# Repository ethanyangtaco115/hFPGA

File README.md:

# hFPGA (WIP)

A modified PicoEVB FPGA board made for rapid prototyping, DIY projects, and making FPGAs more accessible to hobbyists
Sub-System of our Flash LiDAR Project

## Acknowledgements

 - [Major Credit to PicoEVB creators, who made the base schematic for our design.](https://github.com/RHSResearchLLC/PicoEVB/tree/master)

## Features

- 78 Total I/O Pins
- SPI Flash Boot capability
- Integrated USB-JTAG support
- 4 ADC Pins
- 4 Clock Output Pins
- 4 3.3v PWR Pins
- 6 True Single-Ended GPIO Pins
- 15 Differential Lines, with Pseudo-Single Ended capability
- 24 GND Pins

# Authors

Created by [Ethan Yang](https://github.com/ethanyangtaco115) & [Stanley Wang](https://github.com/GhostWinterOwl)

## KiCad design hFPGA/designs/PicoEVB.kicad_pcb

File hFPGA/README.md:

# hFPGA (WIP)

A modified PicoEVB FPGA board made for rapid prototyping, DIY projects, and making FPGAs more accessible to hobbyists

## Acknowledgements

 - [Major Credit to PicoEVB creators, who made the base schematic for our design.](https://github.com/RHSResearchLLC/PicoEVB/tree/master)

## Features

- 78 Total I/O Pins
- SPI Flash Boot capability
- Integrated USB-JTAG support
- 4 ADC Pins
- 4 Clock Output Pins
- 4 3.3v PWR Pins
- 6 True Single-Ended GPIO Pins
- 15 Differential Lines, with Pseudo-Single Ended capability
- 24 GND Pins

# Authors

Created by [Ethan Yang](https://github.com/ethanyangtaco115) & [Stanley Wang](https://github.com/GhostWinterOwl)

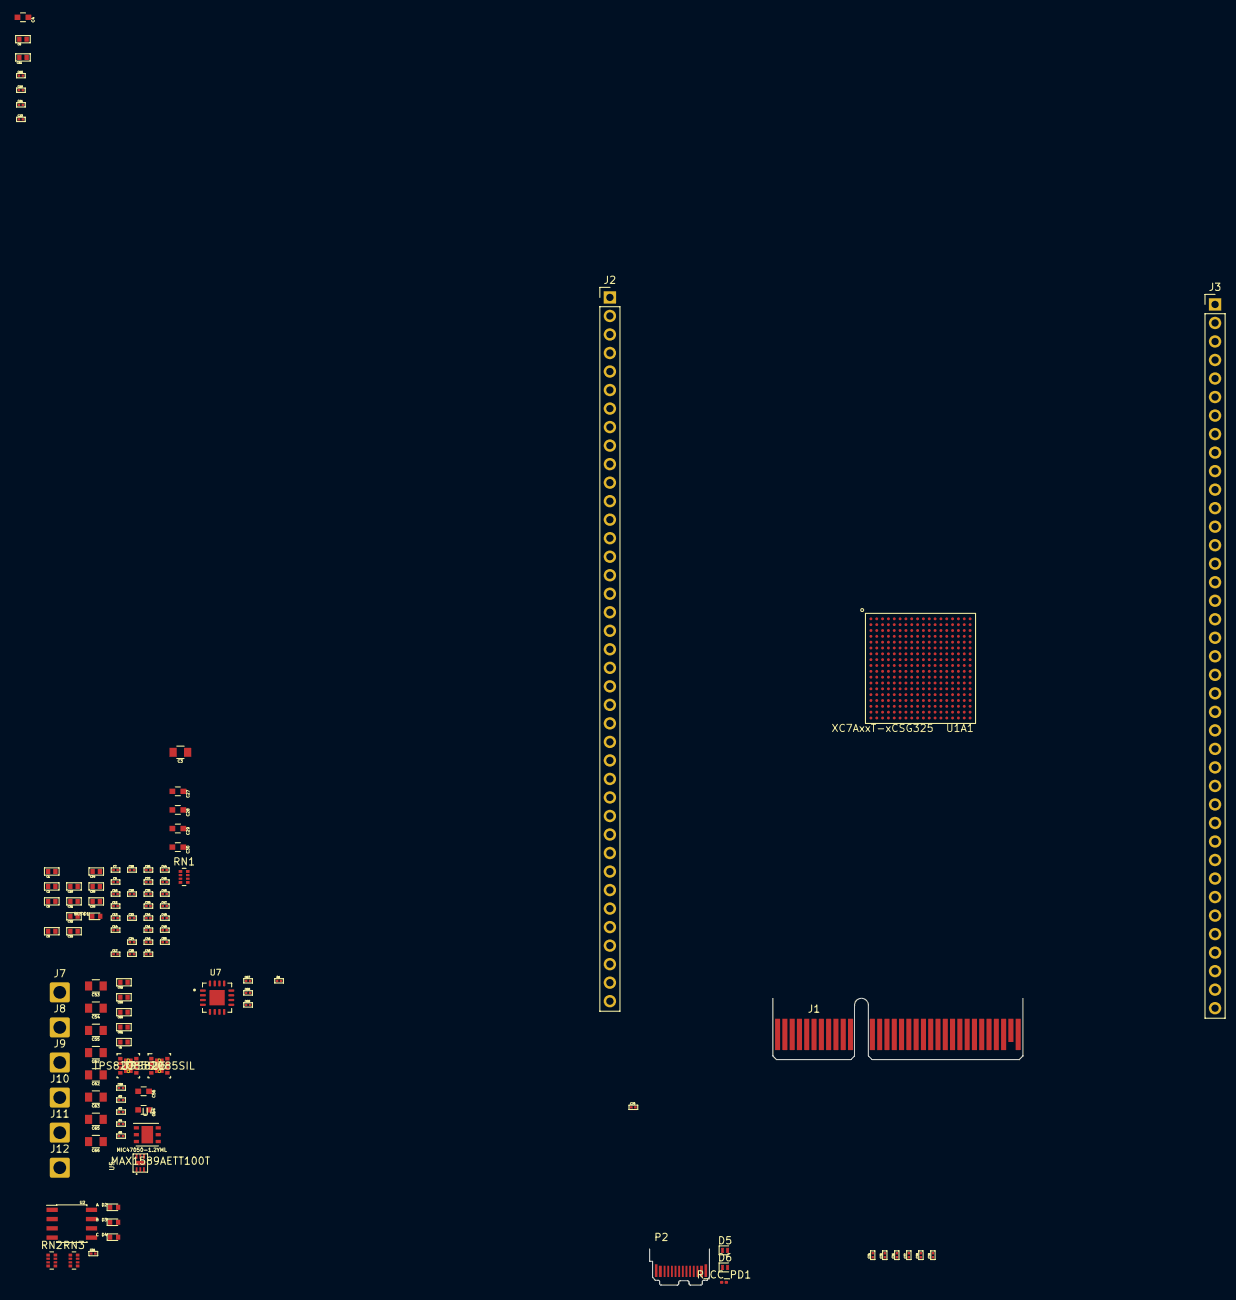
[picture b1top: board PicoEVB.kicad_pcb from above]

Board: 4 copper layers, 109 parts (0 on the bottom side), 35 nets, no tracks yet.

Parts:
C1, C2, C5, C6, C8, C11, C15, C31, C32, C33, C34, C35, C36: 4.7uf; c_0402
C3, C53, C54, C55, C57, C62, C63, C65, C66: 100uf; C_0805
C4, C27, C28, C29, C30: 47uf; C_0603
C7, C12, C16, C17, C18, C19, C20, C21, C22, C23, C24, C25, C26, C37, C38, C39, C40, C41, C42, C43, C44, C45, C46, C47, C48, C49, C50, C70: 0.47uf; c_0201_least
C9, C10, C13, C14, C51, C59, C67, C68, C69, C74, C75, C76, C77, C78, C79: 0.1uf; c_0201_least
C52, C58, C60, C61: 10uf; c_0402
C56, C64: 22uf; C_0603
D1: BUSY; LED_0402
D2: A; LED_0402
D3: B; LED_0402
D4: C; LED_0402
D5, D6: PESD5V0S1UL; D_SOD-882
J1: Bus_PCI_Express_x4; BUS_PCIexpress_x4
J2, J3: 2.54mm Through-Hole Socket; PinHeader_1x39_P2.54mm_Vertical
J7: 3P3; SolderWire-1sqmm_1x01_D1.4mm_OD2.7mm
J8: 1P8; SolderWire-1sqmm_1x01_D1.4mm_OD2.7mm
J9, J11: 1P0; SolderWire-1sqmm_1x01_D1.4mm_OD2.7mm
J10: 1P2; SolderWire-1sqmm_1x01_D1.4mm_OD2.7mm
J12: GND; SolderWire-1sqmm_1x01_D1.4mm_OD2.7mm
L1: 330; r_0402
P2: USB_C_Plug_USB2.0; USB_C_Plug_JAE_DX07P024AJ1
R1: 100; r_0201_least
R2: 124k; r_0201_least
R3, R5: 100k; r_0201_least
R4: 24.9k; r_0201_least
RN1, RN3: 4.7K; R_Array_Convex_4x0402
RN2: 681; R_Array_Convex_4x0402
R_CC_PD1: 5.1k; R_0201_0603Metric
U1A1: XC7AxxT-xCSG325; CSG-324
U2: S25Q; SOIC-8_3.9x4.9mm_Pitch1.27mm
U3, U6: TPS82085SIL; TPS82084SILR
U4: MAX1589AETT100T
U5: MIC47050-1.2YML; MIC47050-DFN-6-2MM
U7: FT230XQ; QFN65P400X400X80-17N

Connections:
BUSY_LED_PU: D1.2 (A), RN2.5 (R4.2)
FPGA_CCLK_0_B: U1A1.E8 (CCLK_0), U2.6 (SCK)
GND: C1.2, C2.2, C3.2, C4.2, C5.2, C6.2, C7.2, C8.2, C9.2, C10.2, C11.2, C12.2, C13.2, C14.2, C15.2, C16.2, C17.2, C18.2, C19.2, C20.2, C21.2, C22.2, C23.2, C24.2, C25.2, C26.2, C27.2, C28.2, C29.2, C30.2, C31.2, C32.2, C33.2, C34.2, C35.2, C36.2, C37.2, C38.2, C39.2, C40.2, C41.2, C42.2, C43.2, C44.2, C45.2, C46.2, C47.2, C48.2, C49.2, C50.2, C51.2, C52.2, C53.2, C54.2, C55.2, C56.2, C57.2, C58.2, C59.2, C60.2, C61.2, C62.2, C63.2, C64.2, C65.2, C66.2, C67.2, C68.2, C69.2, C70.1, J1.A4 (GND), J1.A12 (GND), J1.A15 (GND), J1.A18 (GND), J1.A20 (GND), J1.A23 (GND), J1.A24 (GND), J1.A27 (GND), J1.A28 (GND), J1.A31 (GND), J1.B4 (GND), J1.B7 (GND), J1.B13 (GND), J1.B16 (GND), J1.B18 (GND), J1.B21 (GND), J1.B22 (GND), J1.B25 (GND), J1.B26 (GND), J1.B29 (GND), J1.B32 (GND), J2.2, J2.5, J2.8, J2.11, J2.14, J2.17, J2.20, J2.23, J2.26, J2.29, J2.32, J2.35, J2.38, J3.8, J3.11, J3.14, J3.17, J3.20, J3.23, J3.26, J3.29, J3.32, J3.35, J3.38, J12.1, P2.A1 (GND), P2.A12 (GND), P2.B1 (GND), P2.B12 (GND), P2.S1 (SHIELD), R3.2, R5.2, R_CC_PD1.2, U1A1.E11 (VCCBATT_0), U1A1.F13 (M2_0), U1A1.J9 (GNDADC_0), U1A1.K9 (VREFN_0), U1A1.K10 (VP_0), U1A1.L9 (VN_0), U1A1.L10 (VREFP_0), U1A1.M9 (DXN_0), U1A1.M10 (DXP_0), U1A1.R11 (M1_0), U2.4 (GND), U3.5 (GND), U3.6 (GND), U3.9 (PAD), U4.4 (GND), U4.7 (GND), U5.2 (GND), U5.7 (GND), U6.5 (GND), U6.6 (GND), U6.9 (PAD), U7.3 (GND), U7.13 (GND), U7.17 (GND)
JTAG_TCK_B: U1A1.F8 (TCK_0), U7.15 (TXD)
JTAG_TDI_B: U1A1.T9 (TDI_0), U7.2 (RXD)
JTAG_TDO_B: U1A1.T8 (TDO_0), U7.16 (~RTS)
JTAG_TMS_B: U1A1.R8 (TMS_0), U7.4 (~CTS)
unnamed: D1.1 (K), RN1.8 (R1.2), U1A1.F12 (DONE_0)
unnamed: D2.2 (A), RN2.6 (R3.2)
unnamed: D3.2 (A), RN2.8 (R1.2)
unnamed: D4.2 (A), RN2.7 (R2.2)
unnamed: D5.1 (K), P2.A7 (D-)
unnamed: D6.1 (K), P2.A6 (D+)
unnamed: C77.2, J1.B15 (PETn0)
unnamed: C79.2, J1.B20 (PETn1)
unnamed: C76.2, J1.B14 (PETp0)
unnamed: C78.2, J1.B19 (PETp1)
unnamed: C74.1, J1.A13 (REFCLK+)
unnamed: C75.1, J1.A14 (REFCLK-)
unnamed: P2.A5 (CC), R_CC_PD1.1
unnamed: RN1.7 (R2.2), U1A1.T10 (INIT_B_0)
unnamed: RN1.6 (R3.2), U1A1.P10 (PROGRAM_B_0)
unnamed: RN3.7 (R2.2), U2.7 (DQ3)
unnamed: RN3.6 (R3.2), U2.3 (DQ2)
unnamed: RN3.5 (R4.2), U2.1 (~CS)
unnamed: R2.2, R3.1, U3.7 (FB)
unnamed: C56.1, C57.1, L1.2, R2.1, U3.8 (VOUT), U4.5 (SHDN#), U4.6 (IN), U5.3 (IN)
unnamed: R4.2, R5.1, U6.7 (FB)
P1V0_MGTAVCC_B: C1.1, C9.1, C13.1, C60.1, C62.1, J9.1, U4.1 (OUT)
P1V0_VCC_FPGA_B: C3.1, C5.1, C7.1, C8.1, C12.1, C15.1, C17.1, C18.1, C20.1, C22.1, C24.1, C25.1, C26.1, C64.1, C65.1, C66.1, J11.1, R4.1, U6.8 (VOUT)
P1V2_MGTAVTT_B: C2.1, C10.1, C14.1, C61.1, C63.1, J10.1, R1.2, U5.4 (OUT)
P1V8_FPGA_VCCAUX_B: C4.1, C6.1, C11.1, C16.1, C19.1, C21.1, C23.1, J8.1, L1.1, U1A1.J10 (VCCADC_0)
USB_2+: D6.2 (A), U7.6 (USBDP)
USB_2-: D5.2 (A), U7.7 (USBDM)
VCC_BANK14_B: C27.1, C28.1, C29.1, C30.1, C31.1, C32.1, C33.1, C34.1, C35.1, C36.1, C37.1, C38.1, C39.1, C40.1, C41.1, C42.1, C43.1, C44.1, C45.1, C46.1, C47.1, C48.1, C49.1, C50.1, C51.1, C52.1, C53.1, C54.1, C55.1, C58.1, C59.1, C67.1, C68.1, C69.1, C70.2, J1.A9 (+3.3V), J1.A10 (+3.3V), J1.B8 (+3.3V), J2.1, J2.39, J3.1, J3.39, J7.1, RN1.1 (R1.1), RN1.2 (R2.1), RN1.3 (R3.1), RN1.4 (R4.1), RN2.1 (R1.1), RN2.2 (R2.1), RN2.3 (R3.1), RN2.4 (R4.1), RN3.1 (R1.1), RN3.2 (R2.1), RN3.3 (R3.1), RN3.4 (R4.1), U1A1.E10 (VCCO_0[2]), U1A1.E12 (CFGBVS_0), U1A1.R10 (VCCO_0[2]), U1A1.R12 (M0_0), U2.8 (Vcc), U3.1 (EN), U3.3 (VIN), U3.4 (VIN), U5.1 (BIAS), U5.6 (EN), U6.1 (EN), U6.3 (VIN), U6.4 (VIN), U7.1 (VCCIO), U7.8 (3V3OUT), U7.9 (~RESET), U7.10 (VCC)

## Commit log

2025-09-17 add schematic
2025-09-17 Rename PicoEVB.kicad_pro to design/schematics/PicoEVB.kicad_pro
2025-09-17 Create schematic
2025-09-17 Create placeholder
2025-09-17 add schematics and project file
2025-09-18 finished schematics
2025-09-18 Create asdfasdfasdf
2025-09-20 Create a
2025-09-20 Create kicad_lib
2025-09-26 Add files via upload
    Organized one group power page 2
2025-09-28 Update README.md
    In addition, previous commit, 99% done with power circuits.
2025-09-29 Current Progress as of 28/9/25 22:54
2025-10-01 Add changes
2025-10-02 Commit power circuits for chip
    All power circuits for chip are DONE. In progress: Connecting bottom of board power circuits.
2025-10-03 Finished 3V3 filled zone wiring for all ICs
    IO yet to be wired.
2025-10-06 Completed Power Circuitry
2025-10-07 progress 10% to USB JTAG

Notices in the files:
parts and their libraries:
Copyright 2016 Accelerated Designs. All rights reserved.
